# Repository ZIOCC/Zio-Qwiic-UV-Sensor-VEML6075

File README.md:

# Zio Qwiic UV Sensor (VEML6075)

> This product can be available for purchase [here](https://www.smart-prototyping.com/Zio-Qwiic-UV-Sensor-VEML6075).

> Note: This sensor is referenced from [Sparkfun's Qwiic VEML6075](https://www.sparkfun.com/products/14748) module's PCB design.

#### Description

This Ultraviolet sensor can be used to detect the intensity of UV A and UV B light waves. The VEML6075 by Vishay has a very good conduct on taking measurements even on a long time solar exposure featuring I2C interface.  It can also output the UVI (Ultraviolet Index, the strength of light radiation at a particular place and time) by doing a simple calculation. The values for UVI range from 0 to 11+, which 6 or above indicate a high radiation index - time to use some sunscreen or even stay indoors!

As most of ZIO boards, it incorporates the Qwiic connector to transfer UV data via I2C, just plug and start taking measurements. Check out the code to setup different UV readings. 

This great little sensor can use either I2C or SPI interfaces so we made it pretty accessible to switch to SPI. Simply solder the header pins provided if you want to!

#### Specification

* Supply Voltage: 3.3V
* Peak Sensitivity UV A: 365nm
* Peak Sensitivity UV B: 330nm
* Operation Temperature Range: -40 to 85°C
* Interface: I2C (address 0x10)
* Dimensions: 20.0 x 20.0mm
* Weight: 1.4g

#### Links

* [VEML6075 Datasheet](https://www.vishay.com/docs/84304/veml6075.pdf)
* [Eagle File and Schematic](https://github.com/ZIOCC/Zio-Qwiic-UV-Sensor-VEML6075)
* [VEML6075 Library](https://github.com/adafruit/Adafruit_VEML6075)

> ###### About Zio
> Zio is a new line of open sourced, compact, and grid layout boards, fully integrated for Arduino and Qwiic ecosystem. Designed ideally for wearables, robotics, small-space limitations or other on the go projects. Check out other awesome Zio products [here](https://www.smart-prototyping.com/Zio).

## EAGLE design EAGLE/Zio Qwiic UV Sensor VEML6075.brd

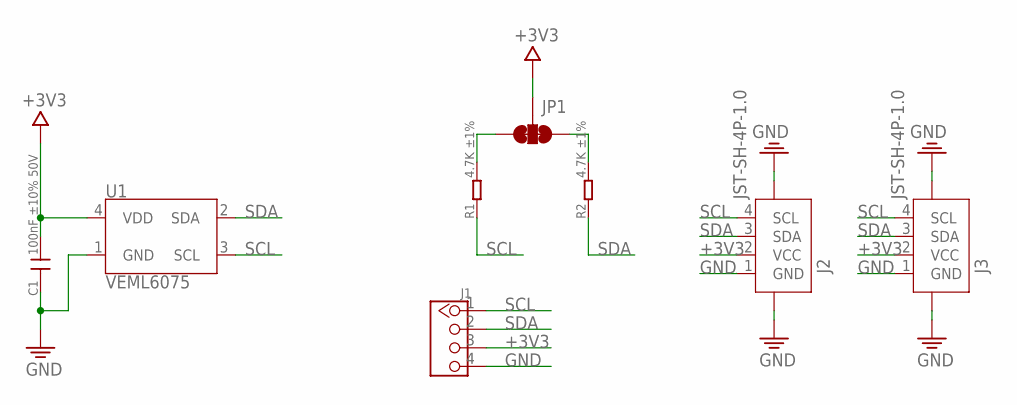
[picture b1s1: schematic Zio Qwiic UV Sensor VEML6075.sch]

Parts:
C1: 100nF ±10% 50V; C0603
J1: HEADER-4P-60/35MIL; 4P-65/35MIL
J2, J3: JST-SH-4P-1.0; JST-SH-4P
JP1: SMT-JUMPER_3_2-NC_TRACE
R1, R2: 4.7K ±1%; R0603
U1: VEML6075; VEML6075_A3OP

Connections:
+3V3: C1.2, J1.3, J2.2 (VCC), J3.2 (VCC), JP1.2, U1.4 (VDD)
GND: C1.1, J1.4, J2.1 (GND), J2.NC1 (5), J2.NC2 (6), J3.1 (GND), J3.NC1 (5), J3.NC2 (6), U1.1 (GND)
unnamed: JP1.3, R1.2
unnamed: JP1.1, R2.2
SCL: J1.1, J2.4 (SCL), J3.4 (SCL), R1.1, U1.3 (SCL)
SDA: J1.2, J2.3 (SDA), J3.3 (SDA), R2.1, U1.2 (SDA)

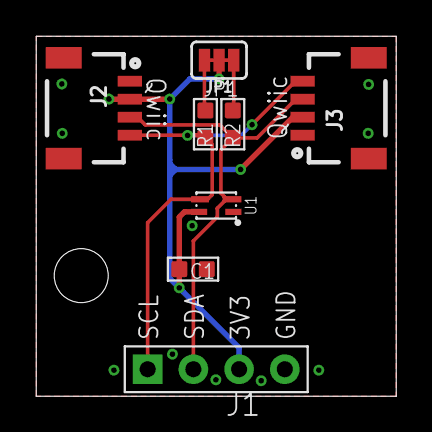
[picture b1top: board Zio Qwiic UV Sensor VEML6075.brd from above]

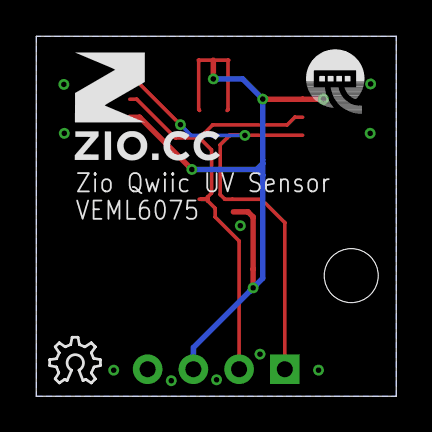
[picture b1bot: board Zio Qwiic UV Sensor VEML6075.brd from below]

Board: 2 copper layers, 20.0 x 20.0 mm, 11 parts (3 on the bottom side), 6 nets.

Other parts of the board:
U$3: 6MM
U$4: OSHW_6X100_NOTEXT
U$5: QWIIC-LOGO-BASIC
